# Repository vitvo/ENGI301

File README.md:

# ENGI301
Repository for ENGI301 course work

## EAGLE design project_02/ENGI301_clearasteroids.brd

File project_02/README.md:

Repository for ENGI 301 Project 2 - Clear Asteroids Game with PocketBeagle
- 

Repository for files of the Clear Asteroids Game PCB. The uploaded files are utilized to manufacture a PCB for the Clear Asteroids Game using the BeagleBoard PocketBeagle. Additional project details can be viewed at: https://github.com/vitvo/ENGI301/blob/master/project_01/README.md

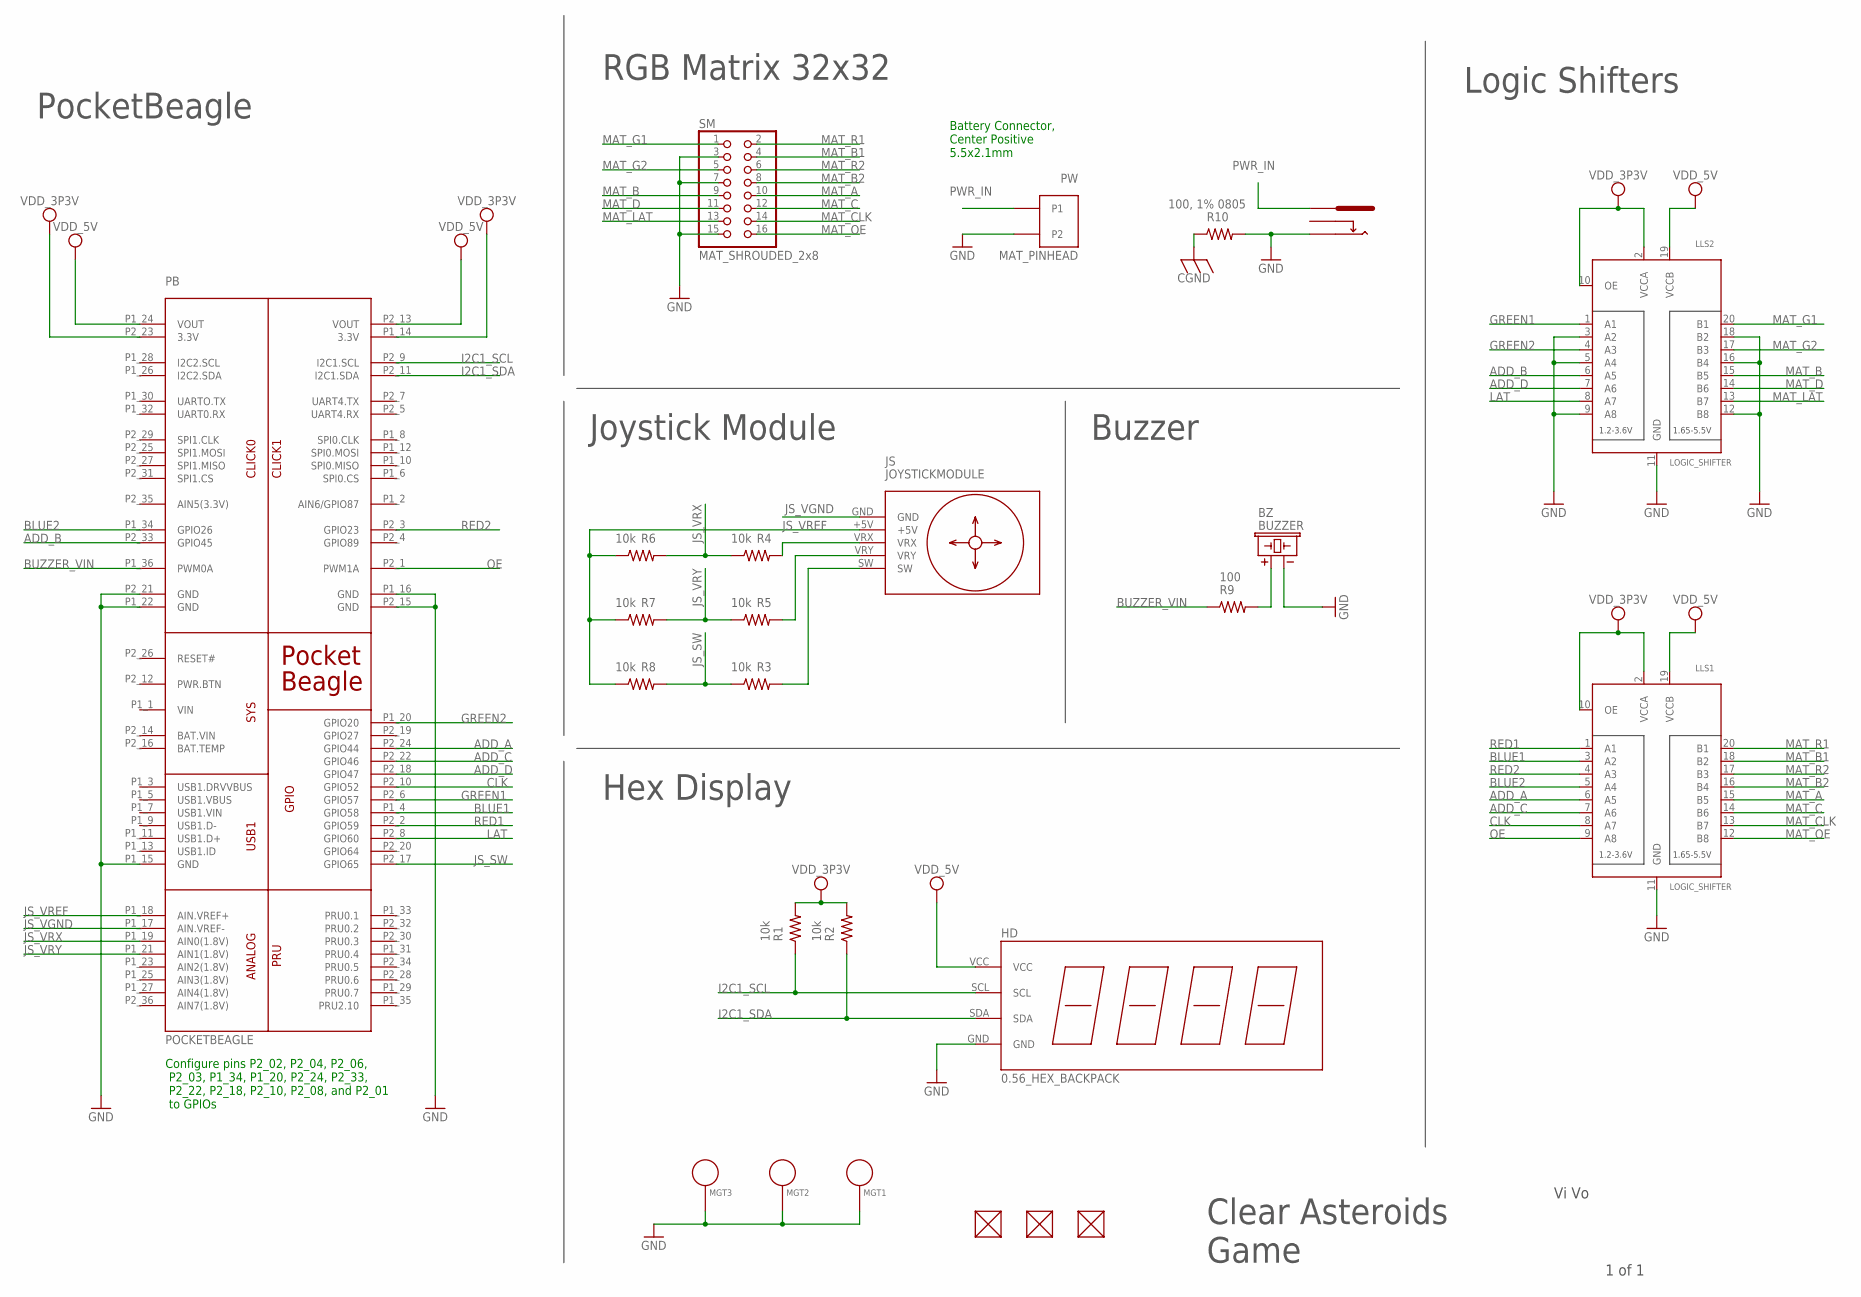
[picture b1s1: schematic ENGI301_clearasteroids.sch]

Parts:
BC: GHI_PJ-102B_POWER_CON
BZ: BUZZER; BUZZER_6.5MM
FUD1, FUD2, FUD3: FIDUCIAL; FIDUCIAL_40MIL
HD: 0.56_HEX_BACKPACK
JS: JOYSTICKMODULE; JOYSTICK-MODULE
LLS1, LLS2: LOGIC_SHIFTER; TSSOP20
MGT1, MGT2, MGT3: MOUNTING_HOLE
PB: POCKETBEAGLE
PW: MAT_PINHEAD; MSHIELD_TERMBLOCK508
R1, R2, R3, R4, R5, R6, R7, R8: 10k; R1206
R9: 100; R1206
R10: 100, 1% 0805; R1206
SM: MAT_SHROUDED_2x8; MICROBUILDER_2X08_SHROUDEDSMT

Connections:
ADD_A: LLS1.6 (A5), PB.P2_24 (GPIO44)
ADD_B: LLS2.6 (A5), PB.P2_33 (GPIO45)
ADD_C: LLS1.7 (A6), PB.P2_22 (GPIO46)
ADD_D: LLS2.7 (A6), PB.P2_18 (GPIO47)
BLUE1: LLS1.3 (A2), PB.P1_4 (GPIO58)
BLUE2: LLS1.5 (A4), PB.P1_34 (GPIO26)
BUZZER_VIN: PB.P1_36 (PWM0A), R9.1
CGND: R10.1
CLK: LLS1.8 (A7), PB.P2_10 (GPIO52)
GND: BC.OUT, BZ.-, HD.GND, LLS1.11 (GND), LLS2.3 (A2), LLS2.5 (A4), LLS2.9 (A8), LLS2.11 (GND), LLS2.12 (B8), LLS2.16 (B4), LLS2.18 (B2), MGT1.P$1, MGT2.P$1, MGT3.P$1, PB.P1_15 (GND), PB.P1_16 (GND), PB.P1_22 (GND), PB.P2_15 (GND), PB.P2_21 (GND), PW.P$4 (P2), R10.2, SM.3, SM.7, SM.15
GREEN1: LLS2.1 (A1), PB.P2_6 (GPIO57)
GREEN2: LLS2.4 (A3), PB.P1_20 (GPIO20)
I2C1_SCL: HD.SCL, PB.P2_9 (I2C1.SCL), R1.1
I2C1_SDA: HD.SDA, PB.P2_11 (I2C1.SDA), R2.1
JS_SW: PB.P2_17 (GPIO65), R3.1, R8.2
JS_VGND: JS.GND, PB.P1_17 (AIN.VREF-)
JS_VREF: JS.+5V, PB.P1_18 (AIN.VREF+), R6.1, R7.1, R8.1
JS_VRX: PB.P1_19 (AIN0(1.8V)), R4.1, R6.2
JS_VRY: PB.P1_21 (AIN1(1.8V)), R5.1, R7.2
LAT: LLS2.8 (A7), PB.P2_8 (GPIO60)
MAT_A: LLS1.15 (B5), SM.10
MAT_B: LLS2.15 (B5), SM.9
MAT_B1: LLS1.18 (B2), SM.4
MAT_B2: LLS1.16 (B4), SM.8
MAT_C: LLS1.14 (B6), SM.12
MAT_CLK: LLS1.13 (B7), SM.14
MAT_D: LLS2.14 (B6), SM.11
MAT_G1: LLS2.20 (B1), SM.1
MAT_G2: LLS2.17 (B3), SM.5
MAT_LAT: LLS2.13 (B7), SM.13
MAT_OE: LLS1.12 (B8), SM.16
MAT_R1: LLS1.20 (B1), SM.2
MAT_R2: LLS1.17 (B3), SM.6
unnamed: BZ.+, R9.2
unnamed: JS.VRX, R4.2
unnamed: JS.VRY, R5.2
unnamed: JS.SW, R3.2
OE: LLS1.9 (A8), PB.P2_1 (PWM1A)
PWR_IN: BC.IN, PW.P$3 (P1)
RED1: LLS1.1 (A1), PB.P2_2 (GPIO59)
RED2: LLS1.4 (A3), PB.P2_3 (GPIO23)
VDD_3P3V: LLS1.2 (VCCA), LLS1.10 (OE), LLS2.2 (VCCA), LLS2.10 (OE), PB.P1_14 (3.3V), PB.P2_23 (3.3V), R1.2, R2.2
VDD_5V: HD.VCC, LLS1.19 (VCCB), LLS2.19 (VCCB), PB.P1_24 (VOUT), PB.P2_13 (VOUT)

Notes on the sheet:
RGB Matrix 32x32
Buzzer
Joystick Module
Logic Shifters
Hex Display
Vi Vo
Clear Asteroids Game
PocketBeagle
Configure pins P2_02, P2_04, P2_06, P2_03, P1_34, P1_20, P2_24, P2_33, P2_22, P2_18, P2_10, P2_08, and P2_01 to GPIOs
Battery Connector, Center Positive 5.5x2.1mm
1 of 1

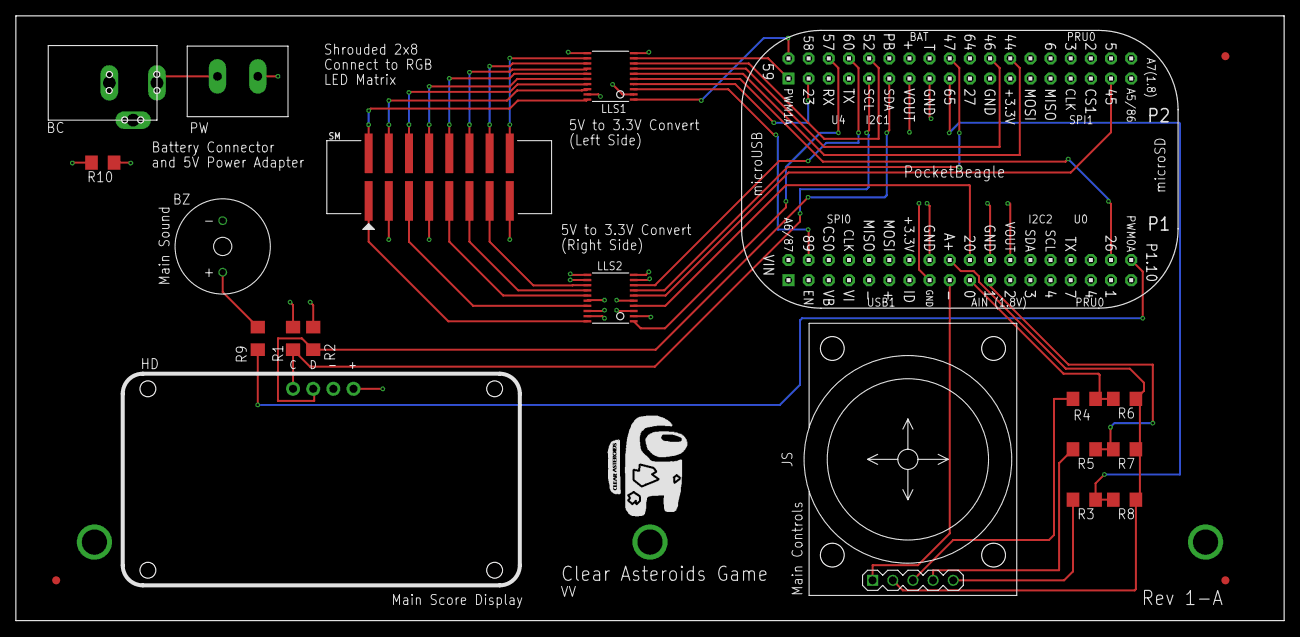
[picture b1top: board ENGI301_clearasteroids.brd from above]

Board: 4 copper layers, 159.8 x 76.2 mm, 25 parts (0 on the bottom side), 42 nets.

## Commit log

2020-09-13 Update README.md
    Updating README.md
2020-09-28 Create simple_calc.py
    Simple calculator in Python compatible with Python2 and 3.
2020-09-28 Create blink_USR3.py
    Blink USR3 LED at 5HZ on PocketBeagle
2020-09-28 Updated blink_USR3.py and simple_calc.py
2020-10-06 Folder containing documentation for project 1
2020-10-06 Revert "Folder containing documentation for project 1"
    This reverts commit 3e65785c29043146e37eacdc72ff08ef71ab3a57.
2020-10-06 Create project_proposal
2020-10-06 Add project 1 proposal PowerPoint
2020-10-13 Add python code for piezzo buzzer to play asteroids sound and Matlab file used to extract the frequencies
2020-10-13 Added extra import for piezzo buzzer
2020-11-13 Rename HitAsteroidsVar1.txt to game_audio_hitasteroids1.txt
2020-11-13 Rename HitAsteroidsVar3.txt to game_audio_hitasteroids2.txt
2020-11-13 Rename HitAsteroidsVar2.txt to game_audio_hitasteroids3.txt
2020-11-13 Rename WeaponFire.txt to game_audio_weaponfire.txt
2020-11-13 Create clear_asteroids_game
2020-11-13 Change file name
2020-11-13 Revert "Change file name"
    This reverts commit 7d671183256b905e8d2d0b3ec042fb15ee6bf4c5.
2020-11-13 Revert "Create clear_asteroids_game"
    This reverts commit 54a7da1be1c251ffc071073f8c8f3df8aee6df45.
2020-11-13 Update and rename project_01/docs/code/piezzobuzzer.py to project_01/docs/asteroids_audo.py
    Edit bugs in the code related to class conventions
2020-11-13 Revert "Update and rename project_01/docs/code/piezzobuzzer.py to project_01/docs/asteroids_audo.py"
    This reverts commit 54717678ce41883b1a624e651f5996b984ba23bc.
2020-11-13 Update and rename piezzobuzzer.py to asteroids_audio.py
    Update name and revise bugs with class name
2020-11-13 Update matrix_display.py
    Fix additional link in usage resources
2020-12-17 Create project_02
2020-12-17 Create docs
2020-12-17 Add files via upload
    Uploaded CAM files
2020-12-17 Revert "Add files via upload"
    This reverts commit 76e89ec68d06bf55da19212d2f009c04de55463e.
2020-12-17 Create Assembly
2020-12-17 Revert "Create Assembly"
    This reverts commit dbaa20407c0e697edb8b26568dd71d7755dac171.
2020-12-17 Uploaded CAM files
2020-12-17 Uploaded EAGLE libraries
2020-12-17 Uploaded schematics
2020-12-17 Reupload bill of materials
